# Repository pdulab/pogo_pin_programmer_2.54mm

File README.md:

# Pogo pin 2.54mm programmer

A simple board with pogo pins. It can be used to program or interface with any board that has exposed pads on a 0.1"/2.54mm pitch grid (maximum grid size of 02x05).
I originally designed it to program another project that has exposed programming pads.

## Features
- Accommodates up to 2x5 pogo pins.
- Extra holes on a 2.54mm (0.1") grid on which alignment pins can be soldered. This makes it easier to align the pogo pins on the pads (if the pads are $n\times2,54mm$ from the side of the PCB).
- Short-circuit protection resistors on each pin. If short circuit protection is not needed, simply solder $0\Omega$ resistors. Resistor size is `1206`.

## Mechanical
- Board size is 35mm x 40mm.
- Mounting holes are 2.5mm in diameter and spaced 25mm x 30mm apart.

## Pictures
Here are some pictures of the board after soldering: 

And an example of how you can use as a programmer (extra programmer hardware not included in this repo):

## License

Copyright pdulab 2025

This project is licensed under [CERN-OHL-W v2](https://cern-ohl.web.cern.ch/).

You may redistribute and modify this documentation and make products using it under the terms of the CERN-OHL-W v2 (https://cern-ohl.web.cern.ch/).
This documentation is distributed WITHOUT ANY EXPRESS OR IMPLIED WARRANTY, INCLUDING OF MERCHANTABILITY, SATISFACTORY QUALITY AND FITNESS FOR A PARTICULAR PURPOSE. Please see the CERN-OHL-W v2 for applicable conditions.

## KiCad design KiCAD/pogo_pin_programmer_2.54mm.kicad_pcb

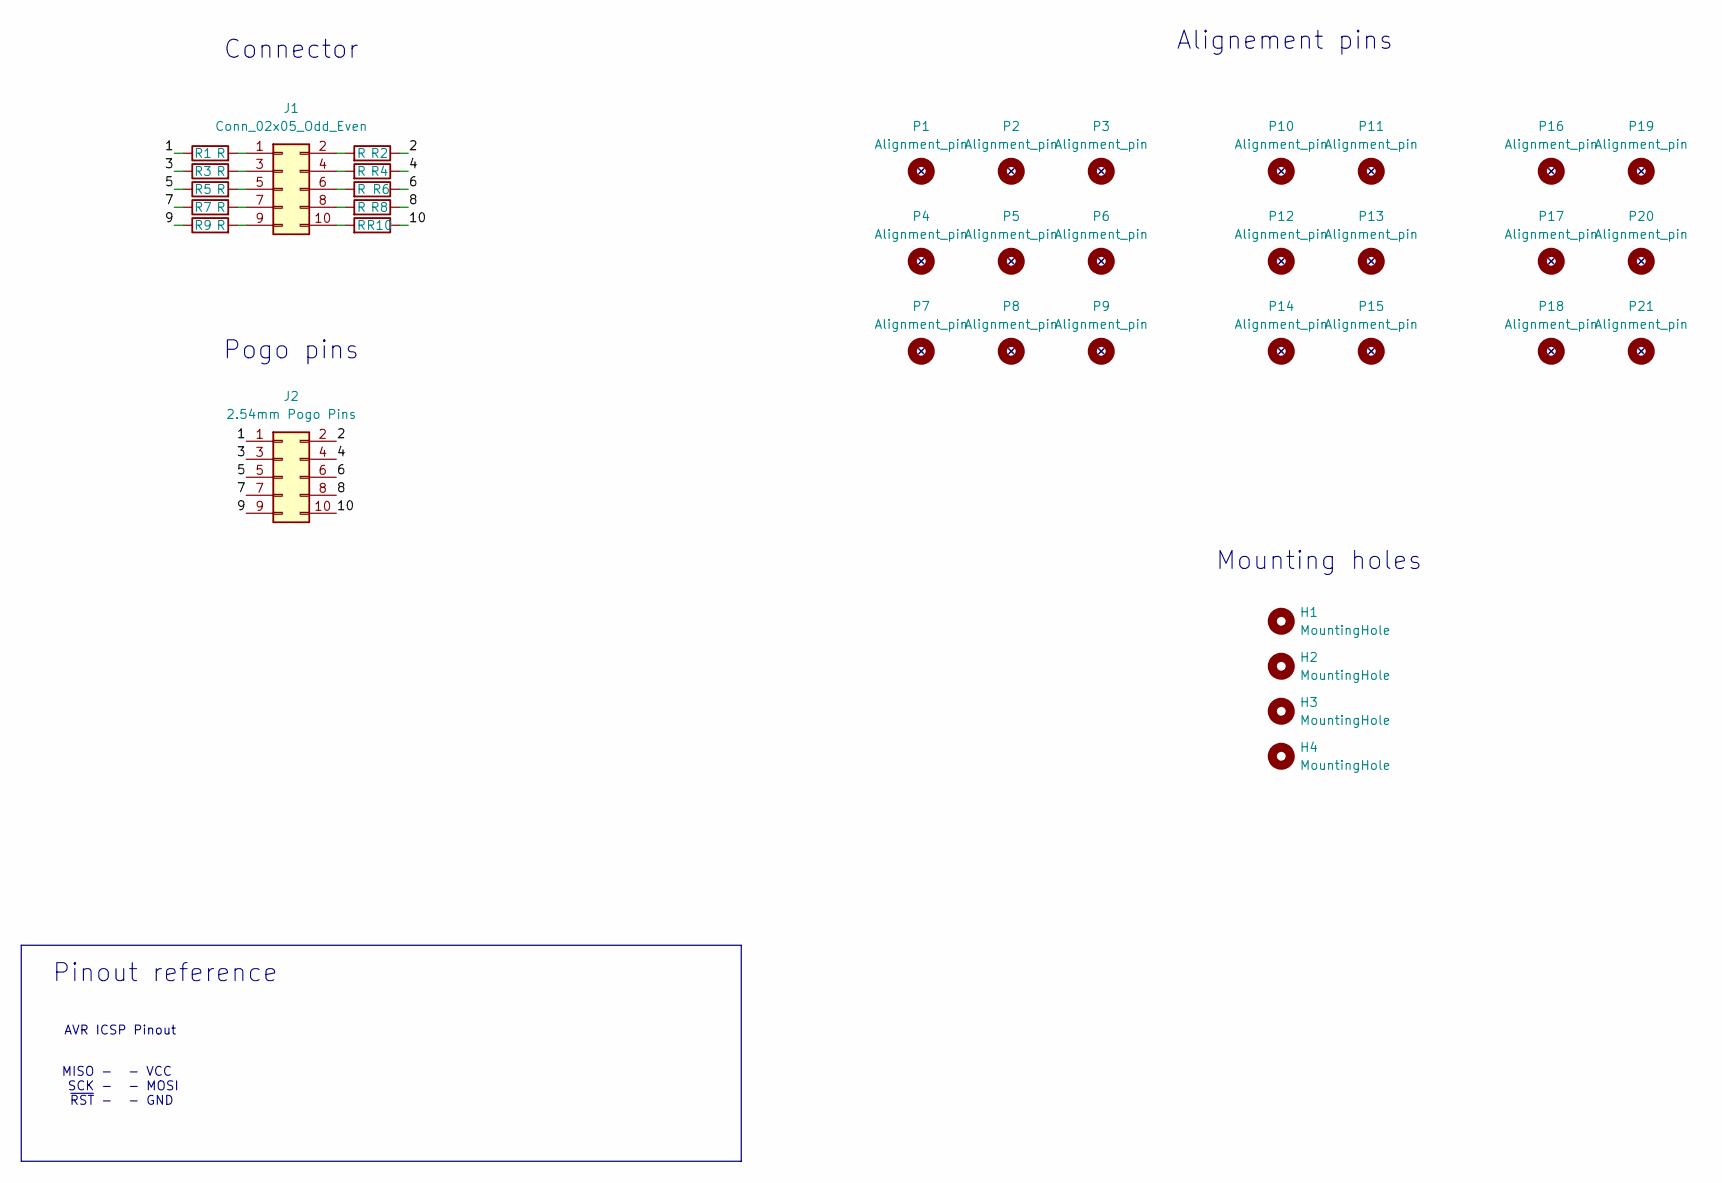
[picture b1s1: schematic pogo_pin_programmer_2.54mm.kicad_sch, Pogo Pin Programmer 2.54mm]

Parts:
H1, H2, H3, H4: MountingHole; MountingHole_2.7mm_M2.5
J1: Conn_02x05_Odd_Even; IDC-Header_2x05_P2.54mm_Vertical
J2: 2.54mm Pogo Pins; PinHeader_2x05_P2.54mm_Vertical
P1, P2, P3, P4, P5, P6, P7, P8, P9, P10, P11, P12, P13, P14, P15, P16, P17, P18, P19, P20, P21: Alignment_pin; Alignment_pin_2.54mm
R1, R2, R3, R4, R5, R6, R7, R8, R9, R10: R; R_1206_3216Metric_Pad1.30x1.75mm_HandSolder

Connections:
/1: J2.1, R1.1
/2: J2.2, R2.1
/3: J2.3, R3.1
/4: J2.4, R4.1
/5: J2.5, R5.1
/6: J2.6, R6.1
/7: J2.7, R7.1
/8: J2.8, R8.1
/9: J2.9, R9.1
/10: J2.10, R10.1
unnamed: J1.1, R1.2
unnamed: J1.2, R2.2
unnamed: J1.3, R3.2
unnamed: J1.4, R4.2
unnamed: J1.5, R5.2
unnamed: J1.6, R6.2
unnamed: J1.7, R7.2
unnamed: J1.8, R8.2
unnamed: J1.9, R9.2
unnamed: J1.10, R10.2

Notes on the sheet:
MISO - SCK - ~{RST} -
Pinout reference
Alignement pins
Pogo pins
AVR ICSP Pinout
Mounting holes
Connector
- VCC - MOSI - GND

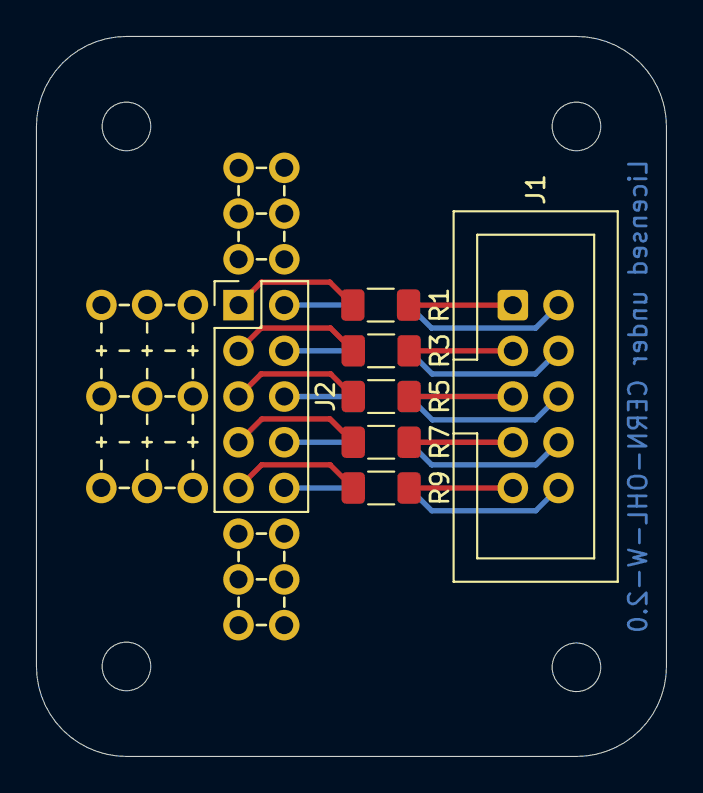
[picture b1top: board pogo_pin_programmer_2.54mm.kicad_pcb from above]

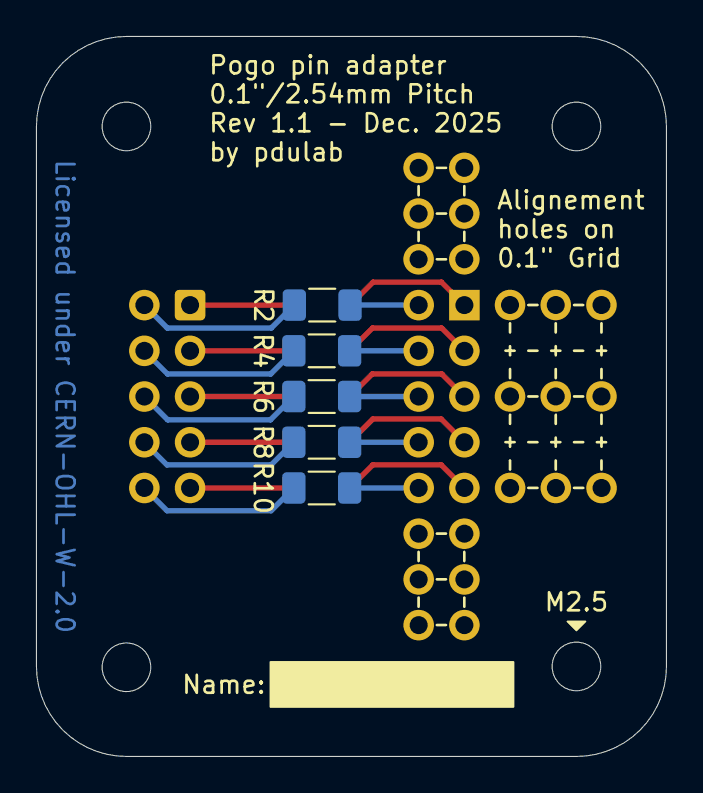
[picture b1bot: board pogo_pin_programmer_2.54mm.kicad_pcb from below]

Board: 2 copper layers, 35.0 x 40.0 mm, 37 parts (26 on the bottom side), 20 nets.

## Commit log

2025-12-28 Fixed license

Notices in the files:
KiCAD/pogo_pin_programmer_2.54mm.kicad_pcb:
Licensed under CERN-OHL-W-2.0
